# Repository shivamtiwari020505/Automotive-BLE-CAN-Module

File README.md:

# Automotive BLE-CAN Module

## PCB views

### TOP PCB

### Isometric PCB view

### Bottom PCB

A four-layer hardware design that connects a vehicle CAN bus to a Bluetooth Low Energy (BLE) interface. The module accepts a 9–36 V vehicle supply and has a separate input for a protected, externally charged 1-cell backup battery. During backup operation, the BLE section remains powered while CAN is unavailable.

This repository is a design snapshot for review and prototyping. It has not been fabricated or electrically tested, and the open items below must be resolved before a fabrication release.

## Design at a glance

| Item | Design |
| --- | --- |
| Vehicle input | 9–36 V |
| CAN interface | CAN FD controller and transceiver, connected to the MCU over SPI |
| Wireless interface | Bluetooth Low Energy, with a U.FL antenna connection |
| Backup input | Protected 1-cell Li-ion pack, charged externally |
| PCB | 49.5 × 56.9 mm, four layers, single-sided component assembly |
| Design tool | KiCad 10.0.6 or later |

## Open the project

1. Open [`hardware/BLE-CAN-module.kicad_pro`](hardware/BLE-CAN-module.kicad_pro) in KiCad 10.0.6 or later.
2. Keep the entire `hardware/` directory together. Its symbol tables, footprint tables, local libraries, and 3D models use project-relative paths.
3. For a quick review without KiCad, see the [schematic PDF](documentation/schematic/BLE-CAN-module-schematic.pdf), [PCB views](documentation/pcb/), and [architecture diagram](documentation/architecture/Architecture.svg).

## Repository layout

| Path | Contents |
| --- | --- |
| [`hardware/`](hardware/) | Editable KiCad schematic and PCB, project-local libraries and 3D models |
| [`hardware/Manufacturing_Output_Files/`](hardware/Manufacturing_Output_Files/) | Gerbers, drill files, placement data, BOM, and fabrication notes |
| [`documentation/architecture/`](documentation/architecture/) | System architecture and block diagram |
| [`documentation/schematic/`](documentation/schematic/) | Schematic PDF |
| [`documentation/pcb/`](documentation/pcb/) | PCB layer plot and 3D views |
| [`documentation/dfmea/`](documentation/dfmea/) | Risk register and review report |

## Design status

The project includes routed PCB files and a manufacturing output package, but these are review artifacts. The [architecture notes](documentation/architecture/ARCHITECTURE.md), [BOM notes](hardware/Manufacturing_Output_Files/BOM/BOM_NOTES.md), and [DFMEA report](documentation/dfmea/DFMEA_REPORT.md) record the remaining assumptions and validation work.

Before fabrication, the main open items are:

- Verify the CAN common-mode choke land pattern and terminal numbering.
- Select the CAN crystal and choose part numbers for the remaining BOM entries.
- Resolve the CAN controller's `nWKRQ` power-domain interface in hardware.
- Confirm the required conformal-coating process for the input-section clearances.

Electrical operation, vehicle transients, thermal behavior, RF performance, and EMC still require prototype testing. Do not treat the included manufacturing files as a production release.

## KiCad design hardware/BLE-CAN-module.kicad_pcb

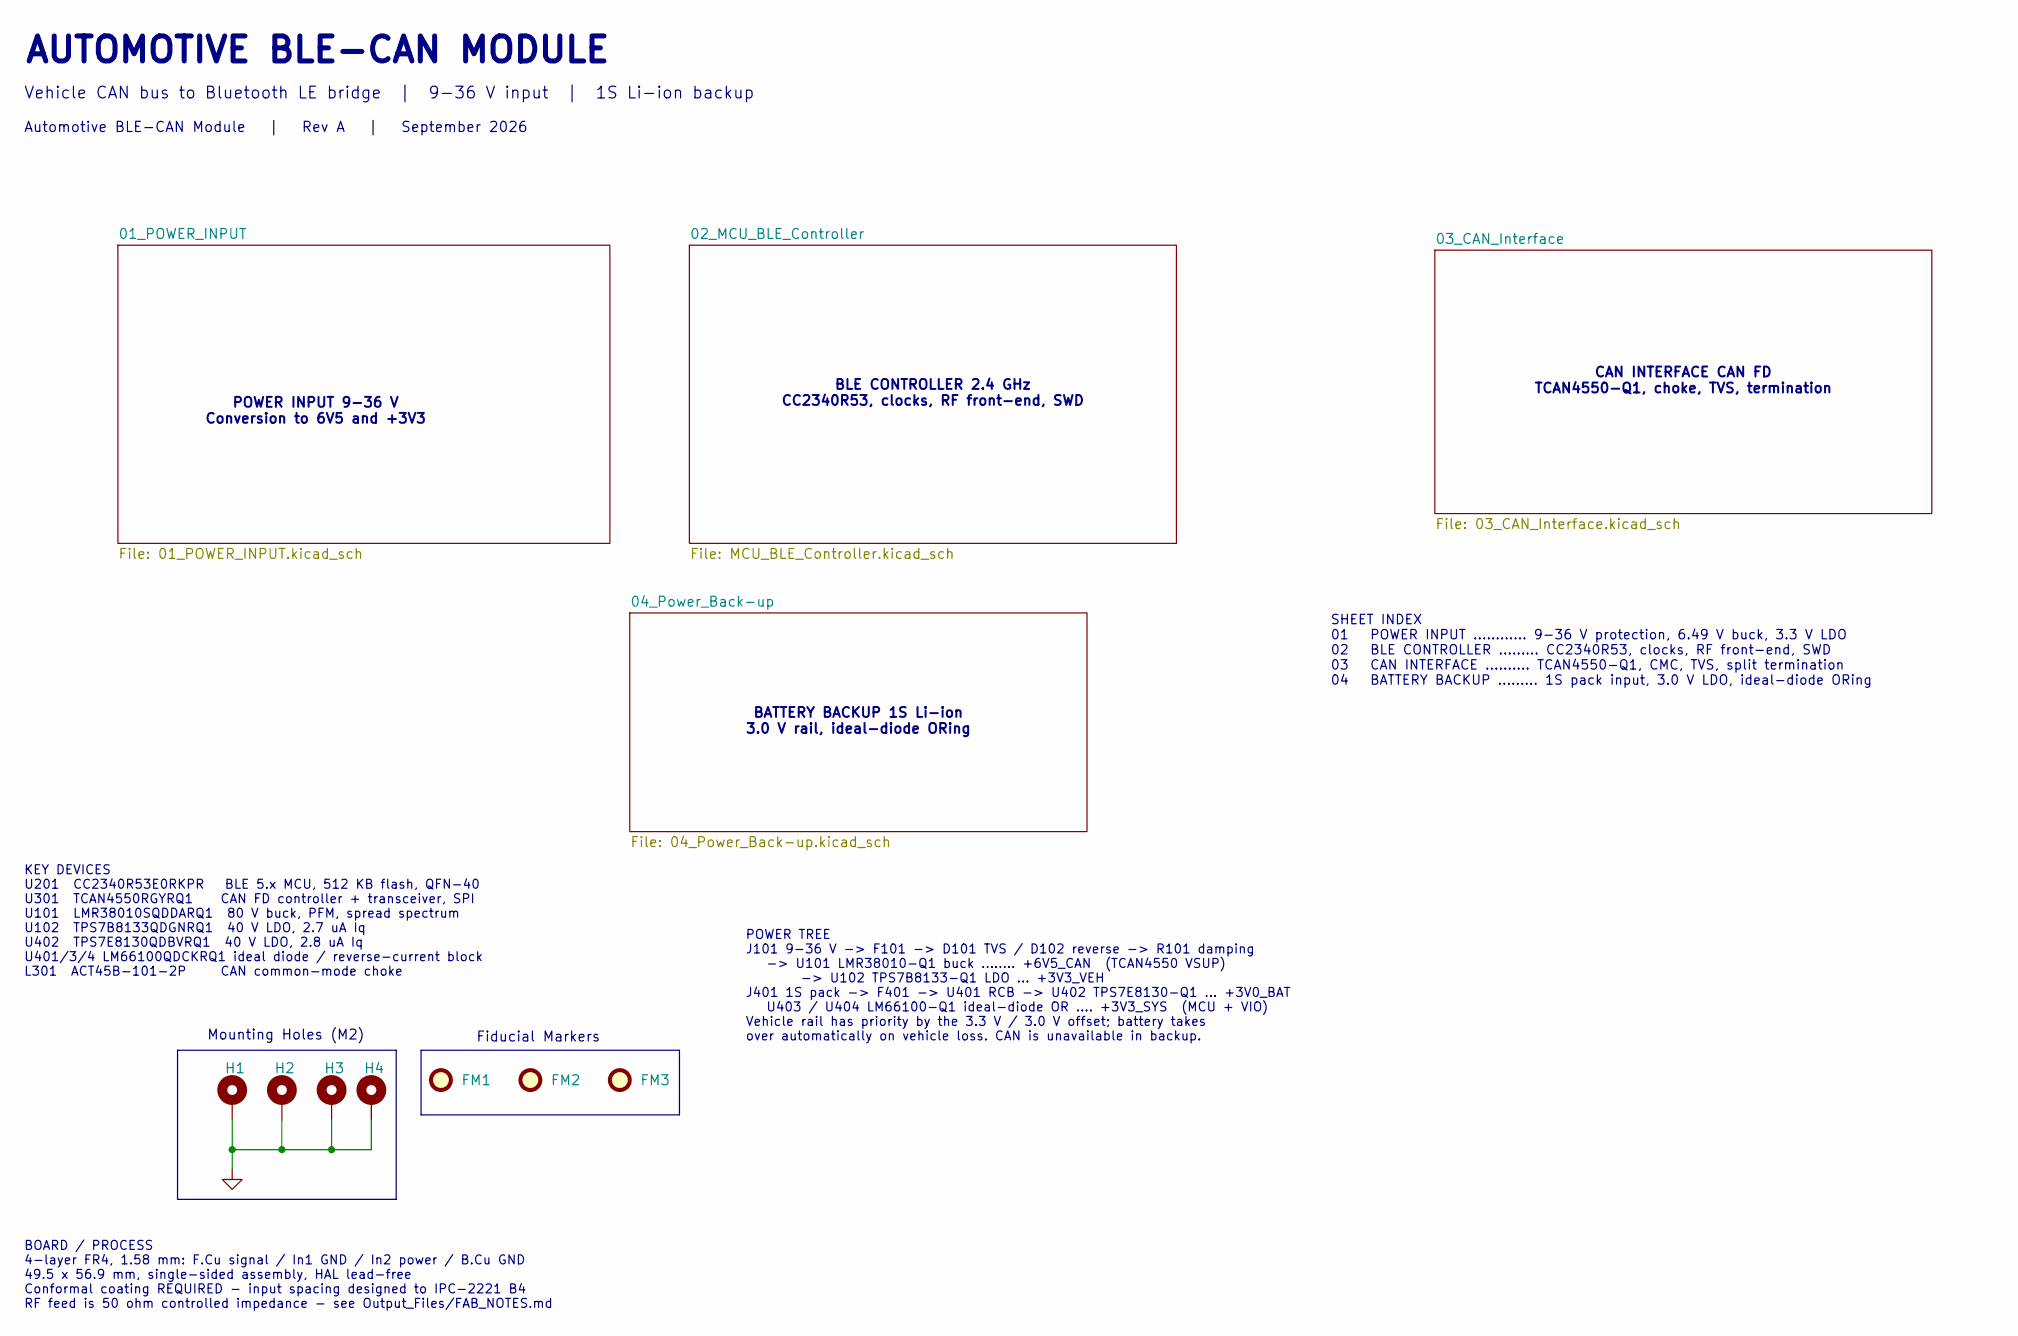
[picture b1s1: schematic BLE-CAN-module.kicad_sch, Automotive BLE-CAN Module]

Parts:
FM1, FM2, FM3: Fiducial; Fiducial_1mm_Mask2mm
H1, H2, H3, H4: MountingHole_Pad; MountingHole_2.2mm_M2_Pad_Via

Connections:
GND: H1.1 (1_1), H2.1 (1_1), H3.1 (1_1), H4.1 (1_1); also elsewhere on the board

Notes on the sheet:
SHEET INDEX 01 POWER INPUT ............ 9-36 V protection, 6.49 V buck, 3.3 V LDO 02 BLE CONTROLLER ......... CC2340R53, clocks, RF front-end, SWD 03 CAN INTERFACE .......... TCAN4550-Q1, CMC, TVS, split termination 04 BATTERY BACKUP ......... 1S pack input, 3.0 V LDO, ideal-diode ORing
POWER INPUT 9-36 V Conversion to 6V5 and +3V3
KEY DEVICES U201 CC2340R53E0RKPR BLE 5.x MCU, 512 KB flash, QFN-40 U301 TCAN4550RGYRQ1 CAN FD controller + transceiver, SPI U101 LMR38010SQDDARQ1 80 V buck, PFM, spread spectrum U102 TPS7B8133QDGNRQ1 40 V LDO, 2.7 uA Iq U402 TPS7E8130QDBVRQ1 40 V LDO, 2.8 uA Iq U401/3/4 LM66100QDCKRQ1 ideal diode /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
Vehicle CAN bus to Bluetooth LE bridge | 9-36 V input | 1S Li-ion backup
POWER TREE J101 9-36 V -> F101 -> D101 TVS / D102 reverse -> R101 damping -> U101 LMR38010-Q1 buck ........ +6V5_CAN (TCAN4550 VSUP) -> U102 TPS7B8133-Q1 LDO ... +3V3_VEH J401 1S pack -> F401 -> U401 RCB -> U402 TPS7E8130-Q1 ... +3V0_BAT U403 / U404 LM66100-Q1 ideal-diode OR .... +3V3_SYS (MCU + VI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
AUTOMOTIVE BLE-CAN MODULE
Mounting Holes (M2)
BOARD / PROCESS 4-layer FR4, 1.58 mm: F.Cu signal / In1 GND / In2 power / B.Cu GND 49.5 x 56.9 mm, single-sided assembly, HAL lead-free Conformal coating REQUIRED - input spacing designed to IPC-2221 B4 RF feed is 50 ohm controlled impedance - see Output_Files/FAB_NOTES.md
Fiducial Markers
Automotive BLE-CAN Module | Rev A | September 2026
BLE CONTROLLER 2.4 GHz CC2340R53, clocks, RF front-end, SWD
CAN INTERFACE CAN FD TCAN4550-Q1, choke, TVS, termination
BATTERY BACKUP 1S Li-ion 3.0 V rail, ideal-diode ORing

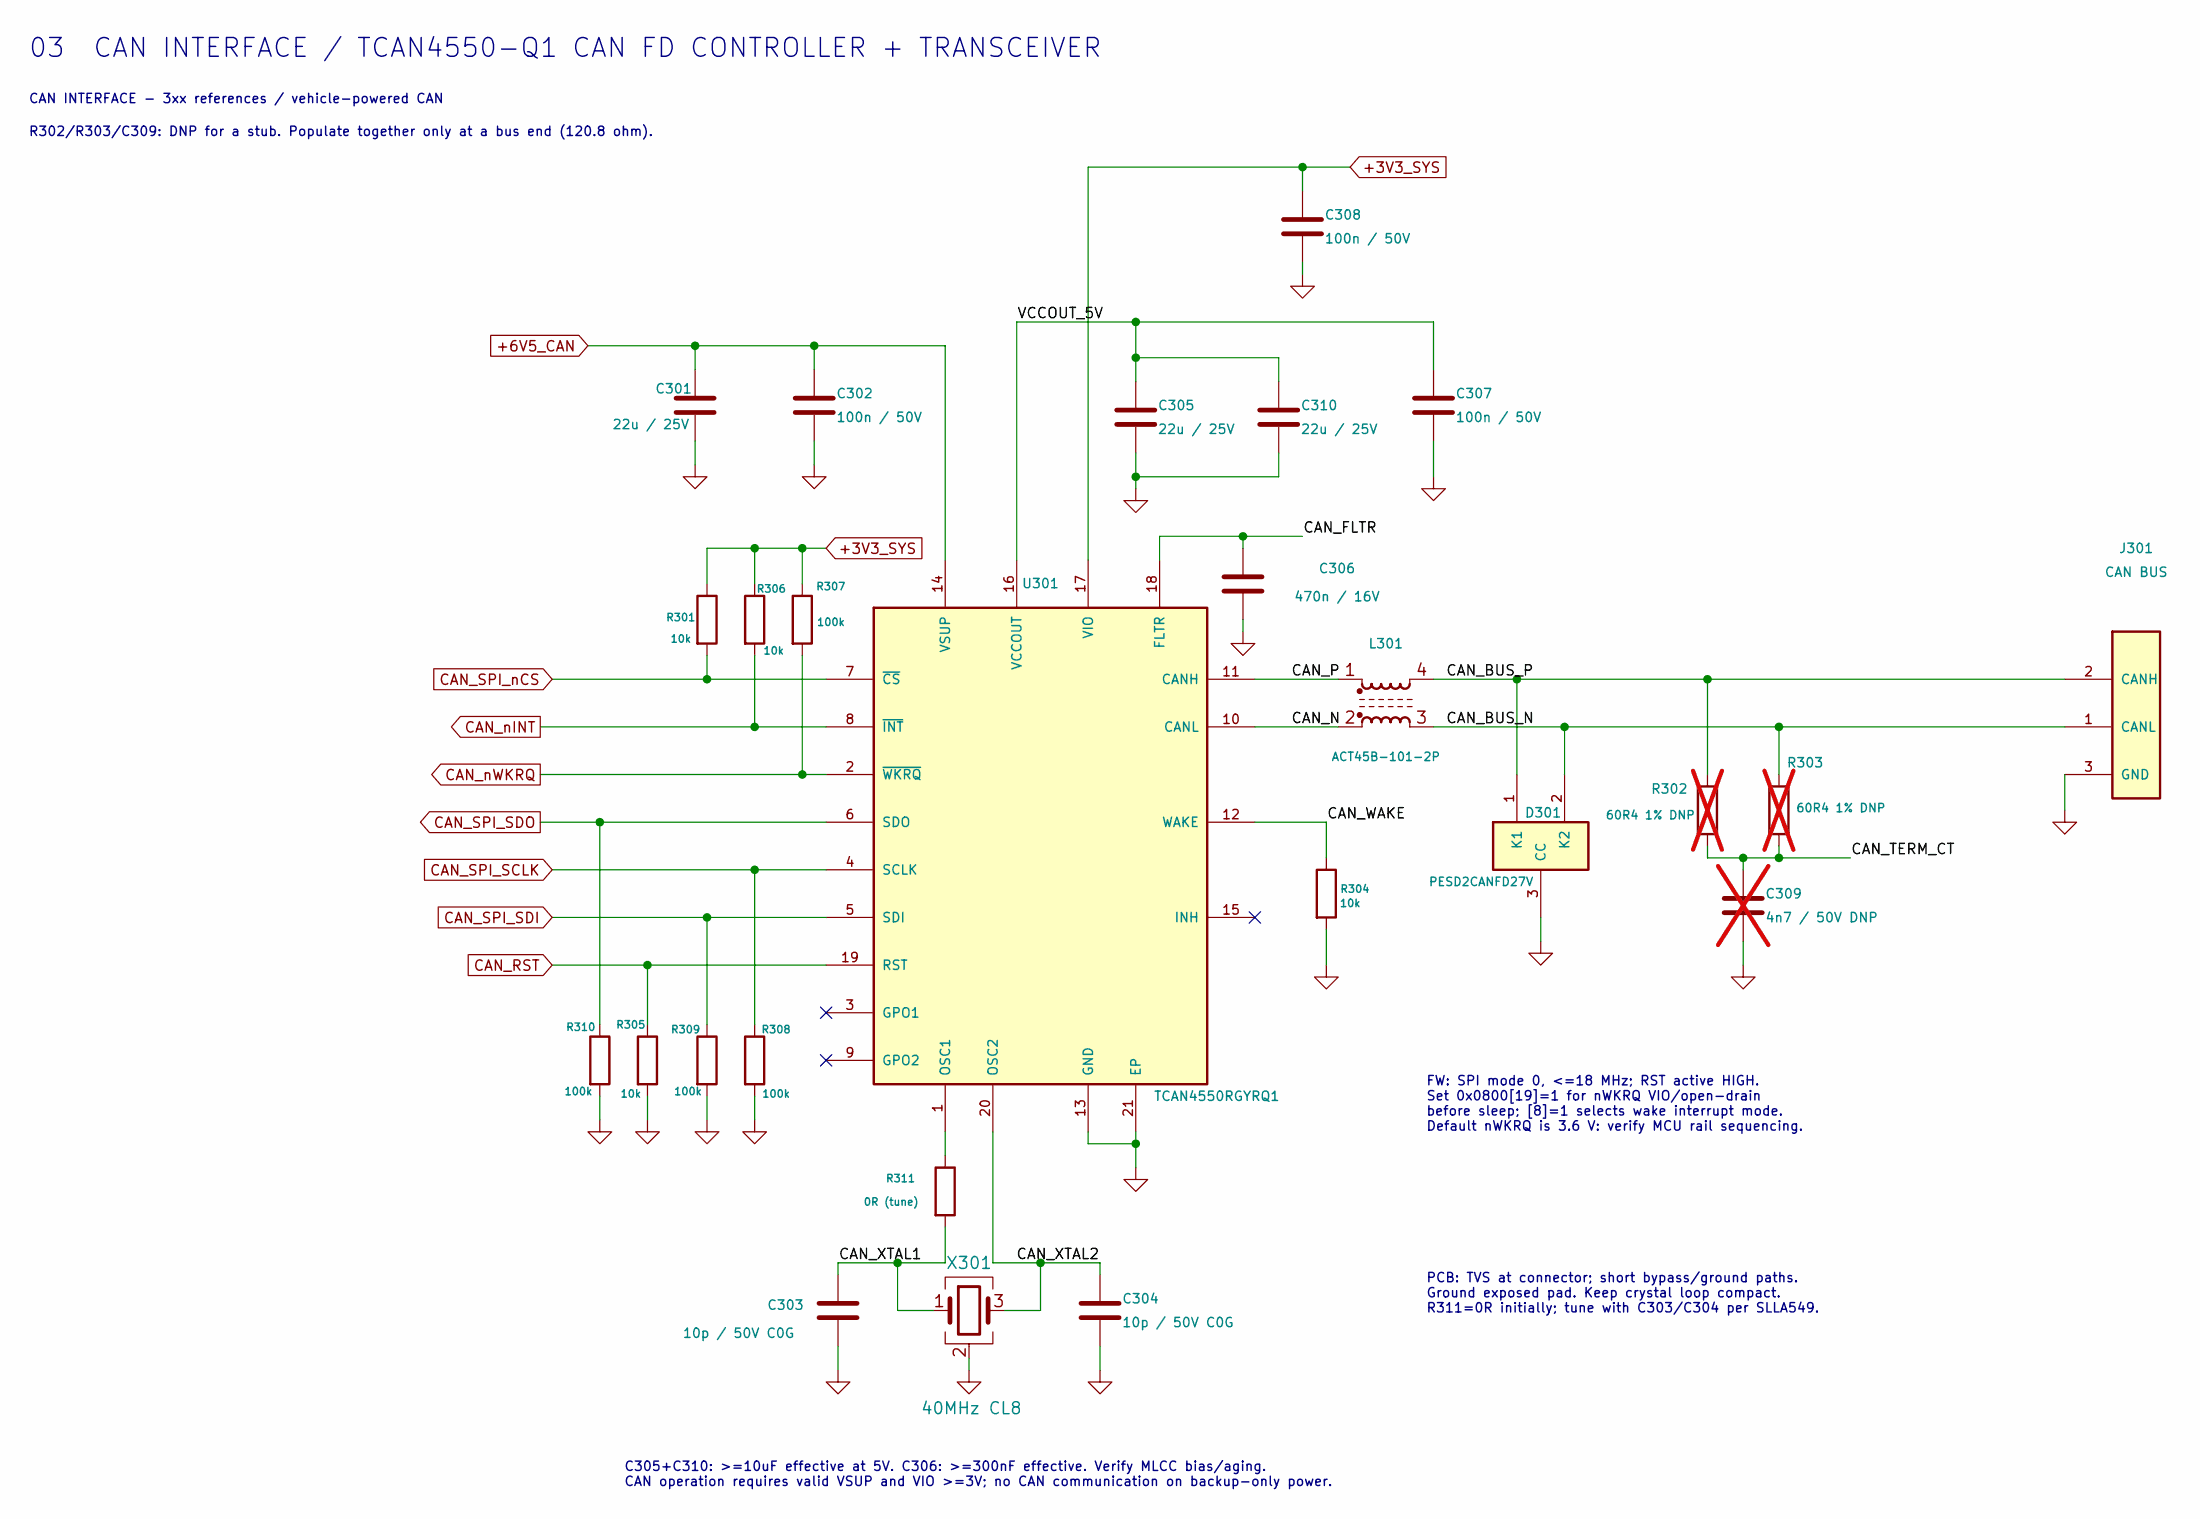
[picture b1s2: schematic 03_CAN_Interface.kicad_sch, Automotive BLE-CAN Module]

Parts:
C301, C305, C310: 22u / 25V; C_1210_3225Metric; MPN CGA6P3X7R1E226M250AB
C302, C307, C308: 100n / 50V; C_0603_1608Metric; MPN CGA3E2X7R1H104K080AA
C303, C304: 10p / 50V C0G; C_0603_1608Metric; MPN CGA3E2C0G1H100D080AA
C306: 470n / 16V; C_0603_1608Metric; MPN CGA3E1X7R1C474K080AC
C309: 4n7 / 50V DNP; C_0603_1608Metric; MPN CGA3E2X7R1H472K080AA; not fitted
D301: PESD2CANFD27V; SOT-23; MPN PESD2CANFD27V-T
J301: CAN BUS; TerminalBlock_Phoenix_MPT-0,5-3-2.54_1x03_P2.54mm_Horizontal; MPN 1725669
L301: ACT45B-101-2P; L_CommonModeChoke_Coilank_ACM4532; MPN ACT45B-101-2P-TL003
R301, R304, R305, R306: 10k; R_0603_1608Metric; MPN CRCW060310K0FKEA
R302, R303: 60R4 1% DNP; R_0805_2012Metric; MPN CRCW080560R4FKEA; not fitted
R307, R308, R309, R310: 100k; R_0603_1608Metric; MPN CRCW0603100KFKEA
R311: 0R (tune); R_0603_1608Metric; MPN CRCW06030000Z0EA
U301: TCAN4550RGYRQ1; TI_RGY0020A_VQFN20; MPN TCAN4550RGYRQ1
X301: 40MHz CL8; Crystal_SMD_2016-4Pin_2.0x1.6mm

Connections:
+3V3_SYS: C308.1, R301.1, R306.1, R307.1, U301.17 (VIO); also elsewhere on the board
+6V5_CAN: C301.1, C302.1, U301.14 (VSUP); also elsewhere on the board
/03_CAN_Interface/CAN_BUS_N: D301.2 (K2), J301.1 (CANL), L301.3, R303.1
/03_CAN_Interface/CAN_BUS_P: D301.1 (K1), J301.2 (CANH), L301.4, R302.1
/03_CAN_Interface/CAN_FLTR: C306.1, U301.18 (FLTR)
/03_CAN_Interface/CAN_N: L301.2, U301.10 (CANL)
/03_CAN_Interface/CAN_P: L301.1, U301.11 (CANH)
/03_CAN_Interface/CAN_TERM_CT: C309.1, R302.2, R303.2
/03_CAN_Interface/CAN_WAKE: R304.1, U301.12 (WAKE)
/03_CAN_Interface/CAN_XTAL1: C303.1, R311.2, X301.1
/03_CAN_Interface/CAN_XTAL2: C304.1, U301.20 (OSC2), X301.3
/03_CAN_Interface/VCCOUT_5V: C305.1, C307.1, C310.1, U301.16 (VCCOUT)
CAN_RST: R305.1, U301.19 (RST); also elsewhere on the board
CAN_SPI_SCLK: R308.1, U301.4 (SCLK); also elsewhere on the board
CAN_SPI_SDI: R309.1, U301.5 (SDI); also elsewhere on the board
CAN_SPI_SDO: R310.1, U301.6 (SDO); also elsewhere on the board
CAN_SPI_nCS: R301.2, U301.7 (~CS); also elsewhere on the board
CAN_nINT: R306.2, U301.8 (~INT); also elsewhere on the board
CAN_nWKRQ: R307.2, U301.2 (~WKRQ); also elsewhere on the board
GND: C301.2, C302.2, C303.2, C304.2, C305.2, C306.2, C307.2, C308.2, C309.2, C310.2, D301.3 (CC), J301.3 (GND), R304.2, R305.2, R308.2, R309.2, R310.2, U301.13 (GND), U301.21 (EP), X301.2 (G), X301.4 (G); also elsewhere on the board
unnamed: R311.1, U301.1 (OSC1)

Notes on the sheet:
03 CAN INTERFACE / TCAN4550-Q1 CAN FD CONTROLLER + TRANSCEIVER
CAN INTERFACE - 3xx references / vehicle-powered CAN
R302/R303/C309: DNP for a stub. Populate together only at a bus end (120.8 ohm).
C305+C310: >=10uF effective at 5V. C306: >=300nF effective. Verify MLCC bias/aging. CAN operation requires valid VSUP and VIO >=3V; no CAN communication on backup-only power.
FW: SPI mode 0, <=18 MHz; RST active HIGH. Set 0x0800[19]=1 for nWKRQ VIO/open-drain before sleep; [8]=1 selects wake interrupt mode. Default nWKRQ is 3.6 V: verify MCU rail sequencing.
PCB: TVS at connector; short bypass/ground paths. Ground exposed pad. Keep crystal loop compact. R311=0R initially; tune with C303/C304 per SLLA549.

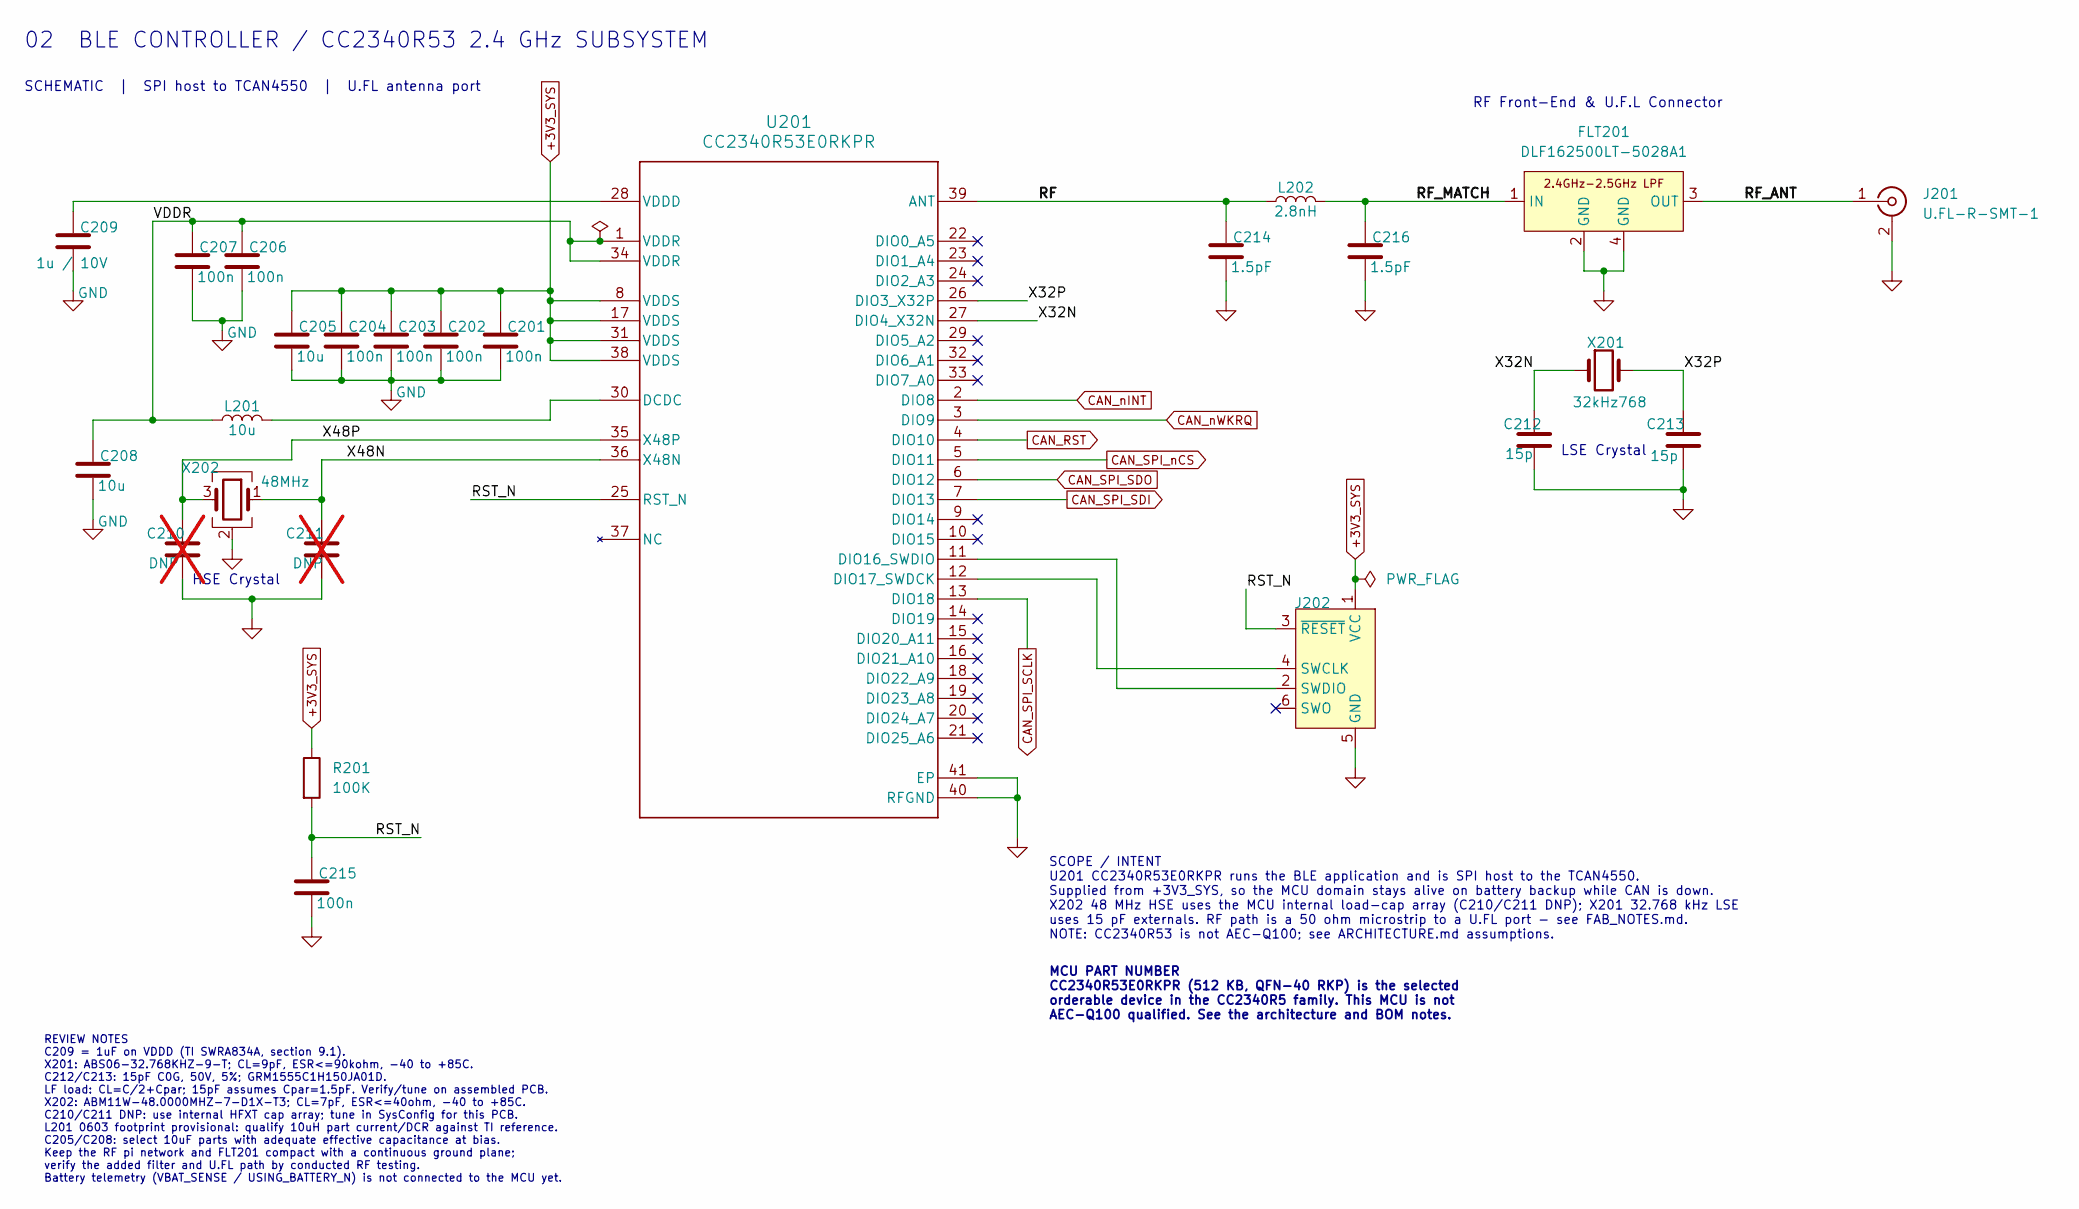
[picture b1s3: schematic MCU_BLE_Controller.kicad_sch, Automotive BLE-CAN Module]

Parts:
C201, C202, C203, C204, C206, C207, C215: 100n; C_0402_1005Metric
C205, C208: 10u; C_0805_2012Metric
C209: 1u / 10V; C_0603_1608Metric
C210, C211: DNP; C_0402_1005Metric; not fitted
C212, C213: 15p; C_0402_1005Metric; MPN GRM1555C1H150JA01D
C214, C216: 1.5pF; C_0402_1005Metric
FLT201: DLF162500LT-5028A1
J201: U.FL-R-SMT-1; U.FL_Hirose_U.FL-R-SMT-1_Vertical
J202: Conn_ARM_SWD_TagConnect_TC2030; Tag-Connect_TC2030-IDC-FP_2x03_P1.27mm_Vertical
L201: 10u; L_0603_1608Metric
L202: 2.8nH; L_0402_1005Metric
R201: 100K; R_0402_1005Metric
U201: CC2340R53E0RKPR; RKP0040B-MFG
X201: 32kHz768; Crystal_SMD_2012-2Pin_2.0x1.2mm; MPN ABS06-32.768KHZ-9-T
X202: 48MHz; Crystal_SMD_2016-4Pin_2.0x1.6mm; MPN ABM11W-48.0000MHZ-7-D1X-T3

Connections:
+3V3_SYS: C201.1, C202.1, C203.1, C204.1, C205.1, J202.1 (VCC), R201.1, U201.8 (VDDS), U201.17 (VDDS), U201.31 (VDDS), U201.38 (VDDS); also elsewhere on the board
/02_MCU_BLE_Controller/RF: C214.1, L202.1, U201.39 (ANT)
/02_MCU_BLE_Controller/RF_ANT: FLT201.3 (OUT), J201.1 (In)
/02_MCU_BLE_Controller/RF_MATCH: C216.1, FLT201.1 (IN), L202.2
/02_MCU_BLE_Controller/RST_N: C215.1, J202.3 (~RESET), R201.2, U201.25 (RST_N)
/02_MCU_BLE_Controller/VDDR: C206.1, C207.1, C208.1, L201.1, U201.1 (VDDR), U201.34 (VDDR)
/02_MCU_BLE_Controller/X32N: C212.1, U201.27 (DIO4_X32N), X201.1
/02_MCU_BLE_Controller/X32P: C213.1, U201.26 (DIO3_X32P), X201.2
/02_MCU_BLE_Controller/X48N: C211.1, U201.36 (X48N), X202.1
/02_MCU_BLE_Controller/X48P: C210.1, U201.35 (X48P), X202.3
CAN_RST: U201.4 (DIO10); also elsewhere on the board
CAN_SPI_SCLK: U201.13 (DIO18); also elsewhere on the board
CAN_SPI_SDI: U201.7 (DIO13); also elsewhere on the board
CAN_SPI_SDO: U201.6 (DIO12); also elsewhere on the board
CAN_SPI_nCS: U201.5 (DIO11); also elsewhere on the board
CAN_nINT: U201.2 (DIO8); also elsewhere on the board
CAN_nWKRQ: U201.3 (DIO9); also elsewhere on the board
GND: C201.2, C202.2, C203.2, C204.2, C205.2, C206.2, C207.2, C208.2, C209.2, C210.2, C211.2, C212.2, C213.2, C214.2, C215.2, C216.2, FLT201.2 (GND), FLT201.4 (GND), J201.2 (Ext), J202.5 (GND), U201.40 (RFGND), U201.41 (EP), X202.2 (G), X202.4 (G); also elsewhere on the board
unnamed: J202.4 (SWCLK), U201.12 (DIO17_SWDCK)
unnamed: J202.2 (SWDIO), U201.11 (DIO16_SWDIO)
unnamed: L201.2, U201.30 (DCDC)
unnamed: C209.1, U201.28 (VDDD)

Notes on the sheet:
SCHEMATIC | SPI host to TCAN4550 | U.FL antenna port
SCOPE / INTENT U201 CC2340R53E0RKPR runs the BLE application and is SPI host to the TCAN4550. Supplied from +3V3_SYS, so the MCU domain stays alive on battery backup while CAN is down. X202 48 MHz HSE uses the MCU internal load-cap array (C210/C211 DNP); X201 32.768 kHz LSE uses 15 pF externals. RF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
LSE Crystal
MCU PART NUMBER CC2340R53E0RKPR (512 KB, QFN-40 RKP) is the selected orderable device in the CC2340R5 family. This MCU is not AEC-Q100 qualified. See the architecture and BOM notes.
REVIEW NOTES C209 = 1uF on VDDD (TI SWRA834A, section 9.1). X201: ABS06-32.768KHZ-9-T; CL=9pF, ESR<=90kohm, -40 to +85C. C212/C213: 15pF C0G, 50V, 5%; GRM1555C1H150JA01D. LF load: CL=C/2+Cpar; 15pF assumes Cpar=1.5pF. Verify/tune on assembled PCB. X202: ABM11W-48.0000MHZ-7-D1X-T3; CL=7pF, ESR<=40oh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
RF Front-End & U.F.L Connector
HSE Crystal
02 BLE CONTROLLER / CC2340R53 2.4 GHz SUBSYSTEM

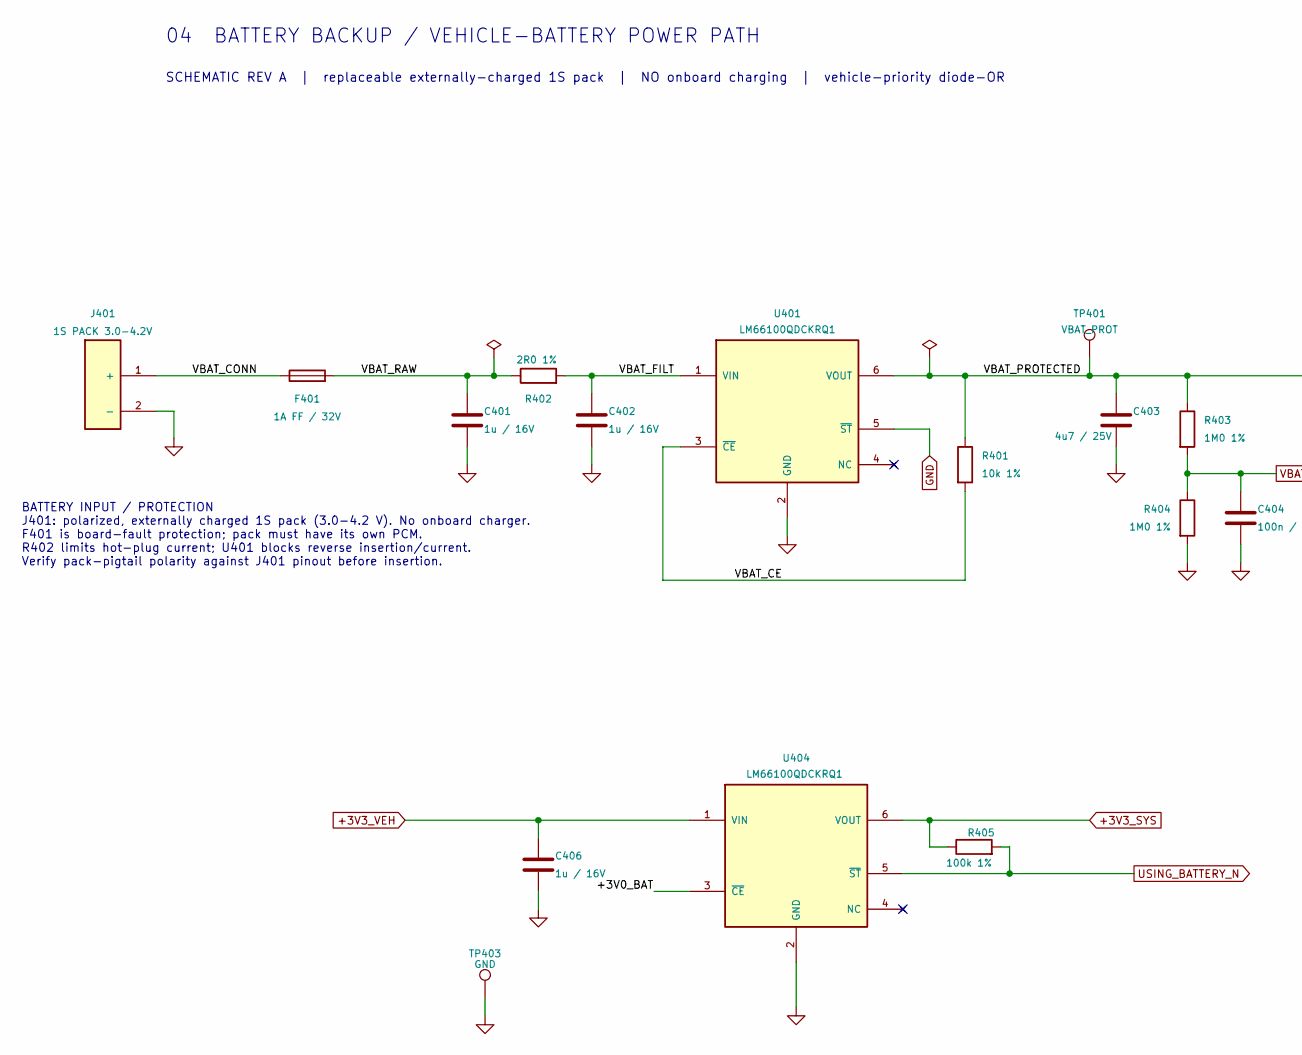
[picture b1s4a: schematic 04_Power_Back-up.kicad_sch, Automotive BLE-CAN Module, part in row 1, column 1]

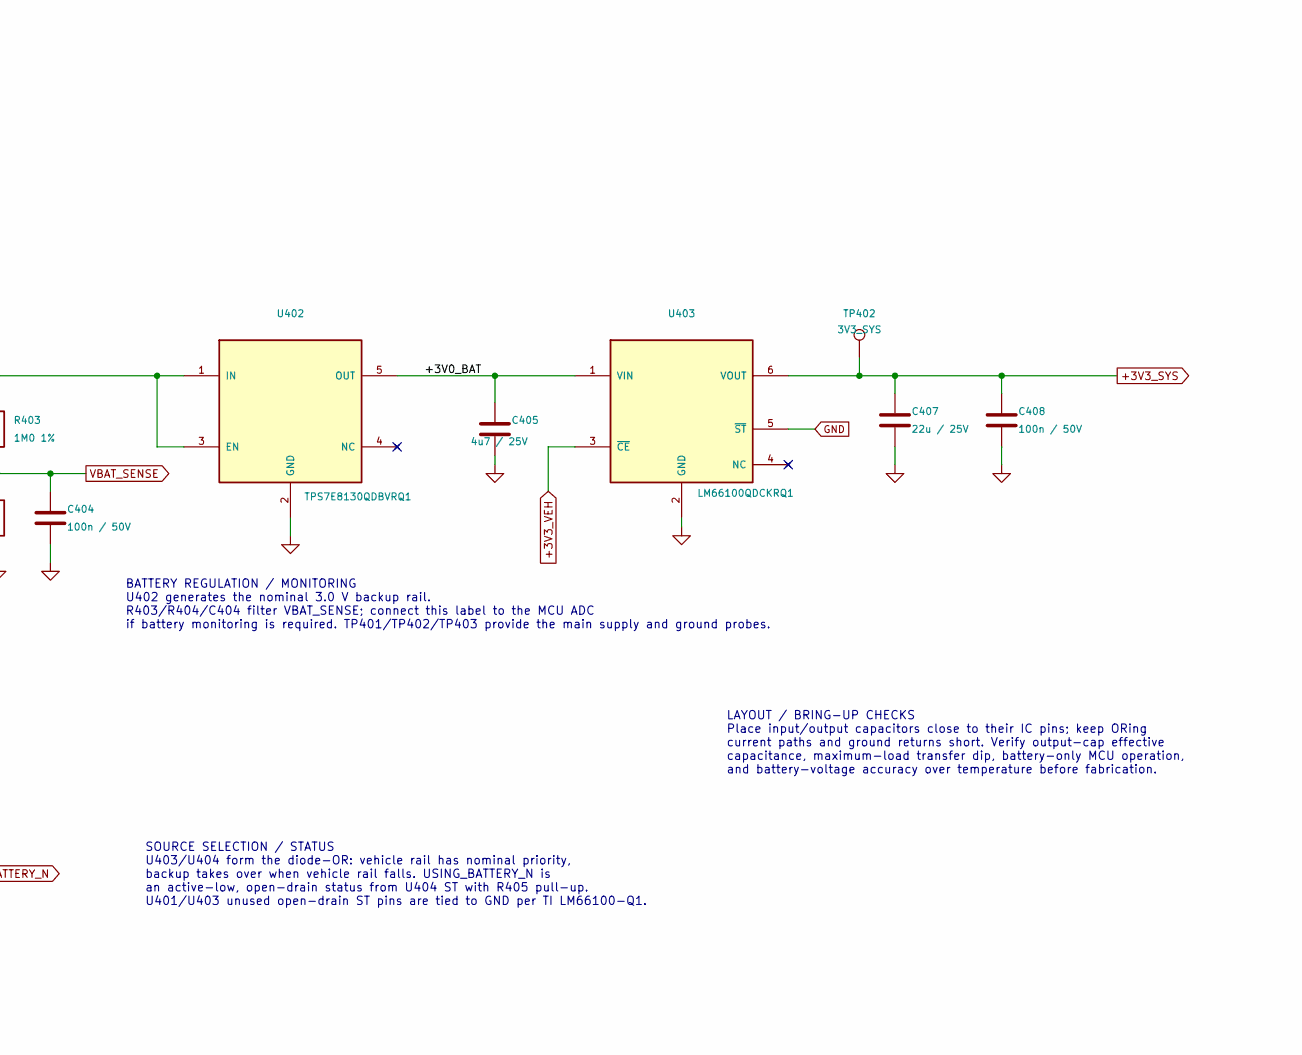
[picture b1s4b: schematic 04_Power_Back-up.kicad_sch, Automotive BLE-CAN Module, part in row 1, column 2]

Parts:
C401, C402, C406: 1u / 16V; C_0603_1608Metric; MPN CGA3E1X7R1C105K080AC
C403, C405: 4u7 / 25V; C_0805_2012Metric; MPN CGA4J1X7R1E475K125AC
C404, C408: 100n / 50V; C_0603_1608Metric; MPN CGA3E2X7R1H104K080AA
C407: 22u / 25V; C_1210_3225Metric; MPN CGA6P3X7R1E226M250AB
F401: 1A FF / 32V; Fuse_0603_1608Metric; MPN MFU0603FF01000P1AT
J401: 1S PACK 3.0-4.2V; JST_PH_S2B-PH-K_1x02_P2.00mm_Horizontal; MPN S2B-PH-K-S(LF)(SN)
R401: 10k 1%; R_0603_1608Metric; MPN CRCW060310K0FKEA
R402: 2R0 1%; R_0603_1608Metric; MPN CRCW06032R00FKEA
R403, R404: 1M0 1%; R_0603_1608Metric; MPN CRCW06031M00FKEA
R405: 100k 1%; R_0603_1608Metric; MPN CRCW0603100KFKEA
TP401: VBAT_PROT; TestPoint_Pad_D2.0mm; MPN N/A - PCB copper pad
TP402: 3V3_SYS; TestPoint_Pad_D2.0mm; MPN N/A - PCB copper pad
TP403: GND; TestPoint_Pad_D2.0mm; MPN N/A - PCB copper pad
U401, U403, U404: LM66100QDCKRQ1; SOT-363_SC-70-6; MPN LM66100QDCKRQ1
U402: TPS7E8130QDBVRQ1; SOT-23-5; MPN TPS7E8130QDBVRQ1

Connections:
+3V3_SYS: C407.1, C408.1, R405.1, TP402.1 (1_1), U403.6 (VOUT), U404.6 (VOUT); also elsewhere on the board
+3V3_VEH: C406.1, U403.3 (~CE), U404.1 (VIN); also elsewhere on the board
/04_Power_Back-up/+3V0_BAT: C405.1, U402.5 (OUT), U403.1 (VIN), U404.3 (~CE)
/04_Power_Back-up/VBAT_CE: R401.2, U401.3 (~CE)
/04_Power_Back-up/VBAT_CONN: F401.1, J401.1 (+)
/04_Power_Back-up/VBAT_FILT: C402.1, R402.2, U401.1 (VIN)
/04_Power_Back-up/VBAT_PROTECTED: C403.1, R401.1, R403.1, TP401.1 (1_1), U401.6 (VOUT), U402.1 (IN), U402.3 (EN)
/04_Power_Back-up/VBAT_RAW: C401.1, F401.2, R402.1
GND: C401.2, C402.2, C403.2, C404.2, C405.2, C406.2, C407.2, C408.2, J401.2 (-), R404.2, TP403.1 (1_1), U401.2 (GND), U401.5 (~ST), U402.2 (GND), U403.2 (GND), U403.5 (~ST), U404.2 (GND); also elsewhere on the board
USING_BATTERY_N: R405.2, U404.5 (~ST)
VBAT_SENSE: C404.1, R403.2, R404.1

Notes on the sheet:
LAYOUT / BRING-UP CHECKS Place input/output capacitors close to their IC pins; keep ORing current paths and ground returns short. Verify output-cap effective capacitance, maximum-load transfer dip, battery-only MCU operation, and battery-voltage accuracy over temperature before fabrication.
SCHEMATIC REV A | replaceable externally-charged 1S pack | NO onboard charging | vehicle-priority diode-OR
BATTERY INPUT / PROTECTION J401: polarized, externally charged 1S pack (3.0-4.2 V). No onboard charger. F401 is board-fault protection; pack must have its own PCM. R402 limits hot-plug current; U401 blocks reverse insertion/current. Verify pack-pigtail polarity against J401 pinout before insertion.
04 BATTERY BACKUP / VEHICLE-BATTERY POWER PATH
BATTERY REGULATION / MONITORING U402 generates the nominal 3.0 V backup rail. R403/R404/C404 filter VBAT_SENSE; connect this label to the MCU ADC if battery monitoring is required. TP401/TP402/TP403 provide the main supply and ground probes.
SOURCE SELECTION / STATUS U403/U404 form the diode-OR: vehicle rail has nominal priority, backup takes over when vehicle rail falls. USING_BATTERY_N is an active-low, open-drain status from U404 ST with R405 pull-up. U401/U403 unused open-drain ST pins are tied to GND per TI LM66100-Q1.
